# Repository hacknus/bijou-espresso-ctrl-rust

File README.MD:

### Bijou Espresso Machine Control Software (Rust Code)

This board controls the Bijou Espresso Machine.  
It is based around an STM32F405 microcontroller that reads out 5 PT100 RTDs (2 wire) using 5 MAX31865 ADCs.  
The temperature values are printed out over USB (CDC virtual COM Port) and shown on the SSD1306 OLED display.  
Two heating elements are controlled (SSR40 solid state relays) with PWM signals.  
Additionally a Buzzer and multiple LEDs can be controlled (PWM).

The software uses freertos-rust (wrapper for rust) and thus requires nightly to compile.  
The embedded-graphics crate is used for the display.

## Flashing the hardware (USB):

Setup a python environment in the project folder and install `pyserial`.

Update the `scripts/enter_bootloader.py` script to use the correct serial port for your system.

Connect the board using USB and then run

```
cargo run --release
```

in your python environment.

## Flashing the hardware (ST-Link debugger):

Create a `.cargo/config.toml` file according to this template:

```toml
[target.thumbv7em-none-eabihf]
runner = "arm-none-eabi-gdb -q -x openocd.gdb"
# uncomment these for other setups
# runner = "gdb-multiarch -q"
# runner = "gdb -q"

rustflags = [
    "-C", "link-arg=-Tlink.x"
]

[build]
target = "thumbv7em-none-eabihf"
```

specify your runner (depends on platform).

Connect the board using an ST-Link V3 (with TagConnect) to a USB port on the computer. Be sure to power the board with
an additional USB-C connector. (ST-Link does not provide power)  
First start the openocd server in a terminal/console window:
```openocd -f interface/stlink.cfg -f target/stm32f4x.cfg```   
Flash/Run the code on the hardware using:  
```cargo run --release```

## Notes on flashing/building

To set up your system, be sure to
follow [this rust embedded stm32 guide](https://docs.rust-embedded.org/discovery/f3discovery/03-setup/index.html)!  
Don't forget to install the [ARM GNU toolchain](https://developer.arm.com/downloads/-/arm-gnu-toolchain-downloads).

Now that the `rust-toolchain.toml` exists, the two steps below might not be necessary.  
Make sure you did
```rustup install nightly``` and
```rustup target add thumbv7em-none-eabihf --toolchain nightly``` to add the target to the nightly toolchain.

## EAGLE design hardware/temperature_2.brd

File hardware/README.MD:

## Electronics Hardware of Bijou Espresso Machine 

The main board schematic can be found in `main.sch` and the pcb layout in `main.brd`.  
The AC power measurement board schematic can be found in `AC_board.sch` and the pcb layout in `AC_board.brd`. This is currently not implemented (in software).  
The temperature readout board schematic can be found in `temperature_2.sch` and the pcb layout in `temperature_2.brd`.  
Issues:
- footprint of the mosfets for the LED (Switch) is faulty, needs to be fixed.
- capacitor missing on encoder
- temperature molex connector is the wrong way around (needs to be soldered from the back)
- attention! usb serial resistors are 22 Ohms, not 220 Ohms!!

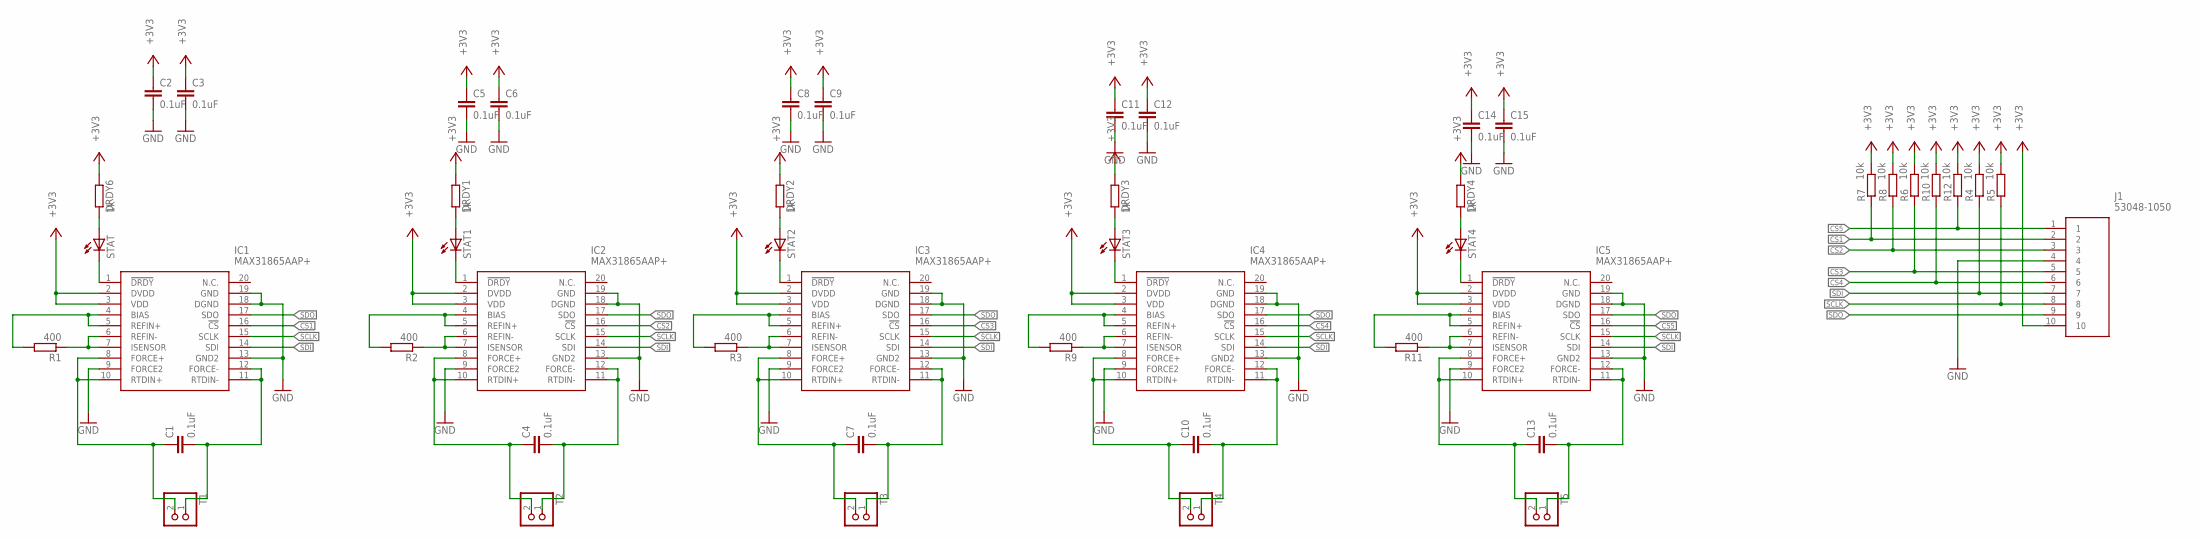
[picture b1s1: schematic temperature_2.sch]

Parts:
C1, C2, C3, C4, C5, C6, C7, C8, C9, C10, C11, C12, C13, C14, C15: 0.1uF; C0603K
DRDY1, DRDY2, DRDY3, DRDY4, DRDY6: 1k; R0603
IC1, IC2, IC3, IC4, IC5: MAX31865AAP+; SOP65P778X199-20N
J1: 53048-1050; SHDRRA10W25P0X125_1X10_1425X55
R1, R2, R3, R9, R11: 400; R1206
R4, R5, R6, R7, R8, R10, R12: 10k; R0603
STAT, STAT1, STAT2, STAT3, STAT4: LEDCHIPLED_0805; CHIPLED_0805
T1, T2, T3, T4, T5: PINHD-1X2; 1X02

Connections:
+3V3: C2.1, C3.1, C5.1, C6.1, C8.1, C9.1, C11.1, C12.1, C14.1, C15.1, DRDY1.1, DRDY2.1, DRDY3.1, DRDY4.1, DRDY6.1, IC1.2 (DVDD), IC1.3 (VDD), IC2.2 (DVDD), IC2.3 (VDD), IC3.2 (DVDD), IC3.3 (VDD), IC4.2 (DVDD), IC4.3 (VDD), IC5.2 (DVDD), IC5.3 (VDD), J1.10, R4.2, R5.2, R6.2, R7.2, R8.2, R10.2, R12.2
CS1: IC1.16 (!CS), J1.2, R7.1
CS2: IC2.16 (!CS), J1.3, R8.1
CS3: IC3.16 (!CS), J1.5, R6.1
CS4: IC4.16 (!CS), J1.6, R10.1
CS5: IC5.16 (!CS), J1.1, R12.1
GND: C2.2, C3.2, C5.2, C6.2, C8.2, C9.2, C11.2, C12.2, C14.2, C15.2, IC1.9 (FORCE2), IC1.13 (GND2), IC1.18 (DGND), IC1.19 (GND), IC2.9 (FORCE2), IC2.13 (GND2), IC2.18 (DGND), IC2.19 (GND), IC3.9 (FORCE2), IC3.13 (GND2), IC3.18 (DGND), IC3.19 (GND), IC4.9 (FORCE2), IC4.13 (GND2), IC4.18 (DGND), IC4.19 (GND), IC5.9 (FORCE2), IC5.13 (GND2), IC5.18 (DGND), IC5.19 (GND), J1.4
unnamed: IC2.4 (BIAS), IC2.5 (REFIN+), R2.2
unnamed: IC2.6 (REFIN-), IC2.7 (ISENSOR), R2.1
unnamed: C4.1, IC2.8 (FORCE+), IC2.10 (RTDIN+), T2.2
unnamed: C4.2, IC2.11 (RTDIN-), IC2.12 (FORCE-), T2.1
unnamed: IC3.4 (BIAS), IC3.5 (REFIN+), R3.2
unnamed: IC3.6 (REFIN-), IC3.7 (ISENSOR), R3.1
unnamed: C7.1, IC3.8 (FORCE+), IC3.10 (RTDIN+), T3.2
unnamed: C7.2, IC3.11 (RTDIN-), IC3.12 (FORCE-), T3.1
unnamed: IC4.4 (BIAS), IC4.5 (REFIN+), R9.2
unnamed: IC4.6 (REFIN-), IC4.7 (ISENSOR), R9.1
unnamed: C10.1, IC4.8 (FORCE+), IC4.10 (RTDIN+), T4.2
unnamed: C10.2, IC4.11 (RTDIN-), IC4.12 (FORCE-), T4.1
unnamed: IC5.4 (BIAS), IC5.5 (REFIN+), R11.2
unnamed: IC5.6 (REFIN-), IC5.7 (ISENSOR), R11.1
unnamed: C13.1, IC5.8 (FORCE+), IC5.10 (RTDIN+), T5.2
unnamed: C13.2, IC5.11 (RTDIN-), IC5.12 (FORCE-), T5.1
unnamed: DRDY6.2, STAT.A
unnamed: IC1.1 (!DRDY), STAT.C
unnamed: DRDY1.2, STAT1.A
unnamed: IC2.1 (!DRDY), STAT1.C
unnamed: DRDY2.2, STAT2.A
unnamed: IC1.4 (BIAS), IC1.5 (REFIN+), R1.2
unnamed: IC1.6 (REFIN-), IC1.7 (ISENSOR), R1.1
unnamed: IC3.1 (!DRDY), STAT2.C
unnamed: C1.1, IC1.8 (FORCE+), IC1.10 (RTDIN+), T1.2
unnamed: C1.2, IC1.11 (RTDIN-), IC1.12 (FORCE-), T1.1
unnamed: DRDY3.2, STAT3.A
unnamed: IC4.1 (!DRDY), STAT3.C
unnamed: DRDY4.2, STAT4.A
unnamed: IC5.1 (!DRDY), STAT4.C
SCLK: IC1.15 (SCLK), IC2.15 (SCLK), IC3.15 (SCLK), IC4.15 (SCLK), IC5.15 (SCLK), J1.8, R5.1
SDI: IC1.14 (SDI), IC2.14 (SDI), IC3.14 (SDI), IC4.14 (SDI), IC5.14 (SDI), J1.7, R4.1
SDO: IC1.17 (SDO), IC2.17 (SDO), IC3.17 (SDO), IC4.17 (SDO), IC5.17 (SDO), J1.9

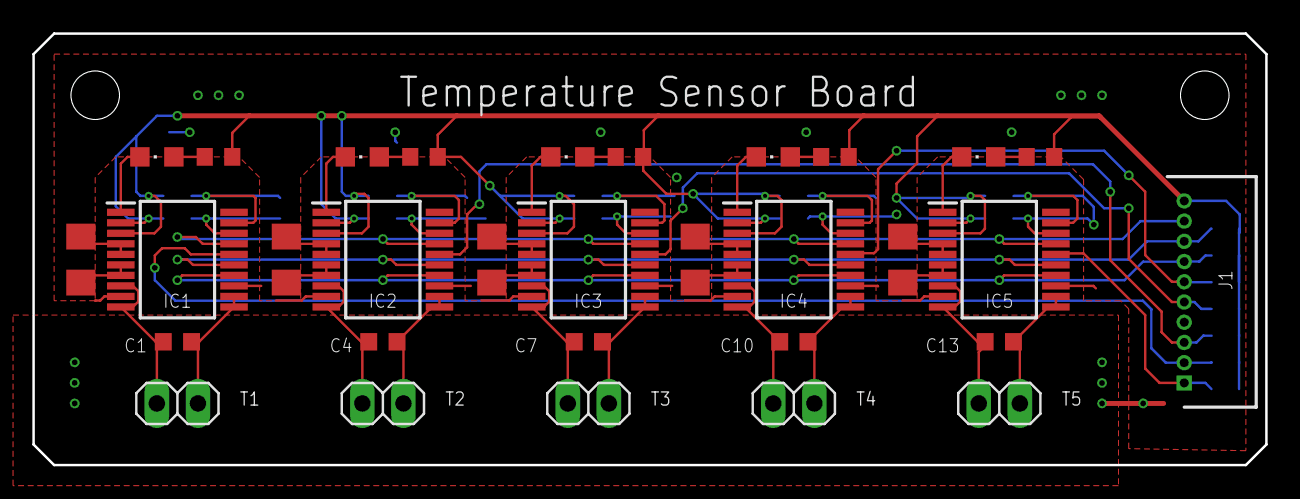
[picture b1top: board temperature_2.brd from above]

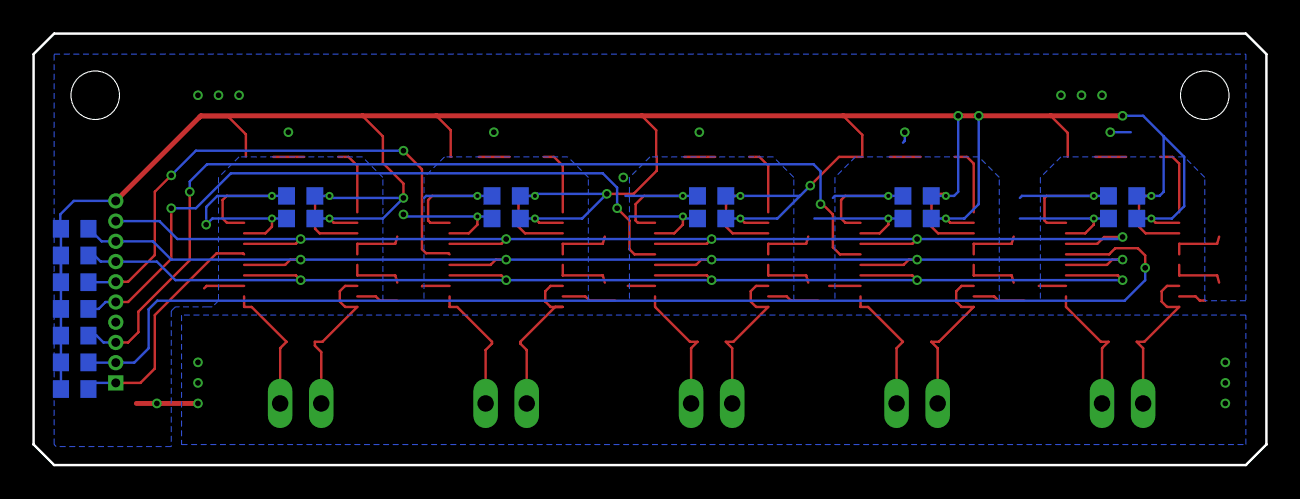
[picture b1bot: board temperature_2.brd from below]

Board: 2 copper layers, 76.2 x 26.7 mm, 48 parts (17 on the bottom side), 40 nets.

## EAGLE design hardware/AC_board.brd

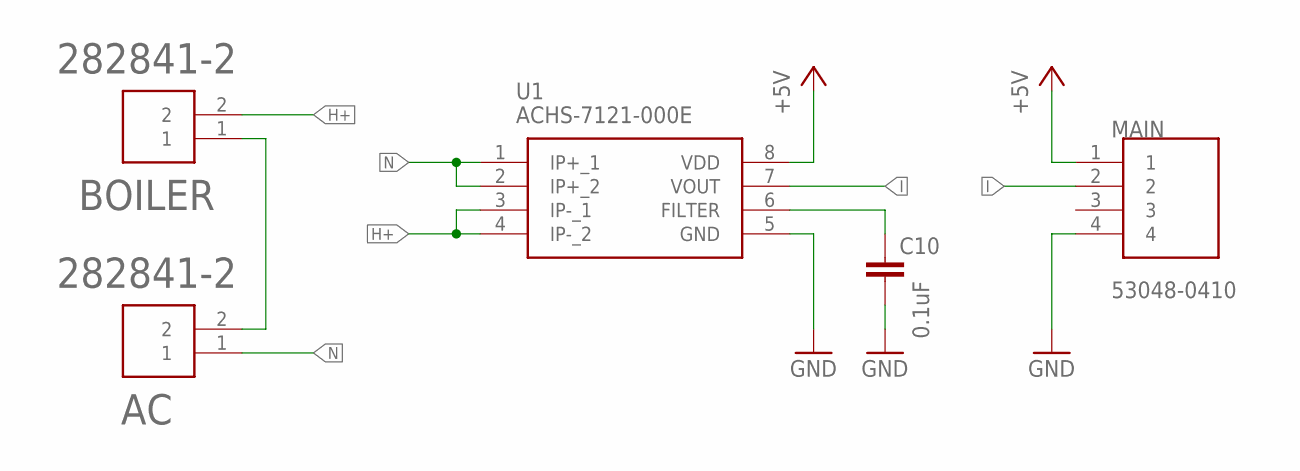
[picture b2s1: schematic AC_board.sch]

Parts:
AC: 282841-2; TE_282841-2
BOILER: 282841-2; TE_282841-2
C10: 0.1uF; C0603K
MAIN: 53048-0410; 530480410
U1: ACHS-7121-000E; SOIC127P606X204-8N

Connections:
+5V: MAIN.1, U1.8 (VDD)
GND: C10.2, MAIN.4, U1.5 (GND)
H+: BOILER.2, U1.3 (IP-_1), U1.4 (IP-_2)
I: MAIN.2, U1.7 (VOUT)
N: AC.1, U1.1 (IP+_1), U1.2 (IP+_2)
unnamed: C10.1, U1.6 (FILTER)
unnamed: AC.2, BOILER.1

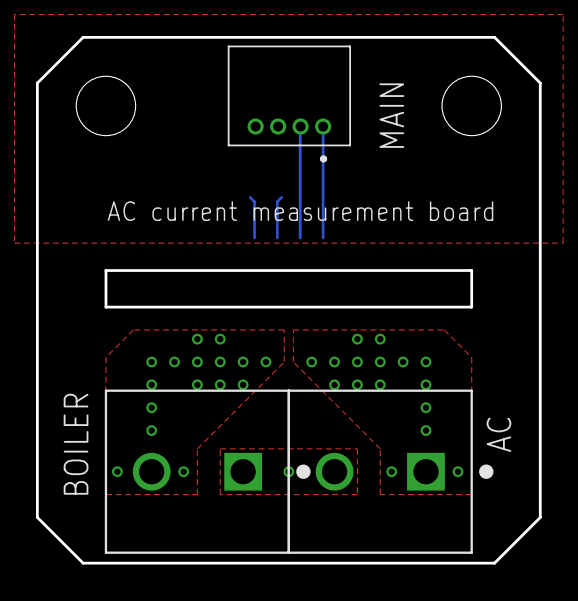
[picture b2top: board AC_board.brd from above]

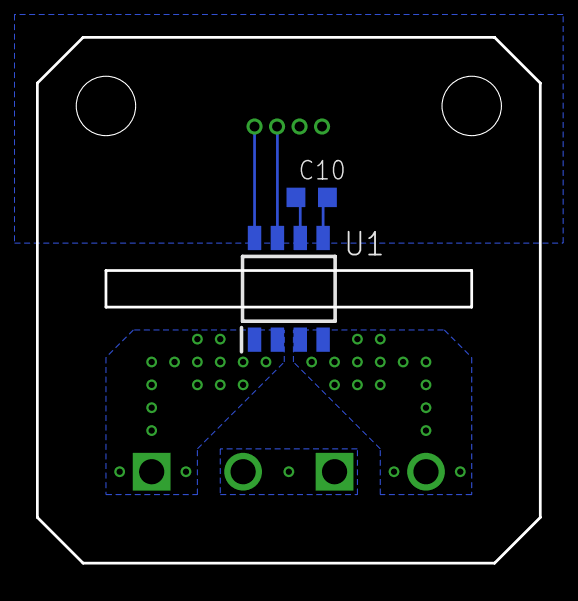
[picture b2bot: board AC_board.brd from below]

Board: 2 copper layers, 27.9 x 29.2 mm, 5 parts (2 on the bottom side), 7 nets.

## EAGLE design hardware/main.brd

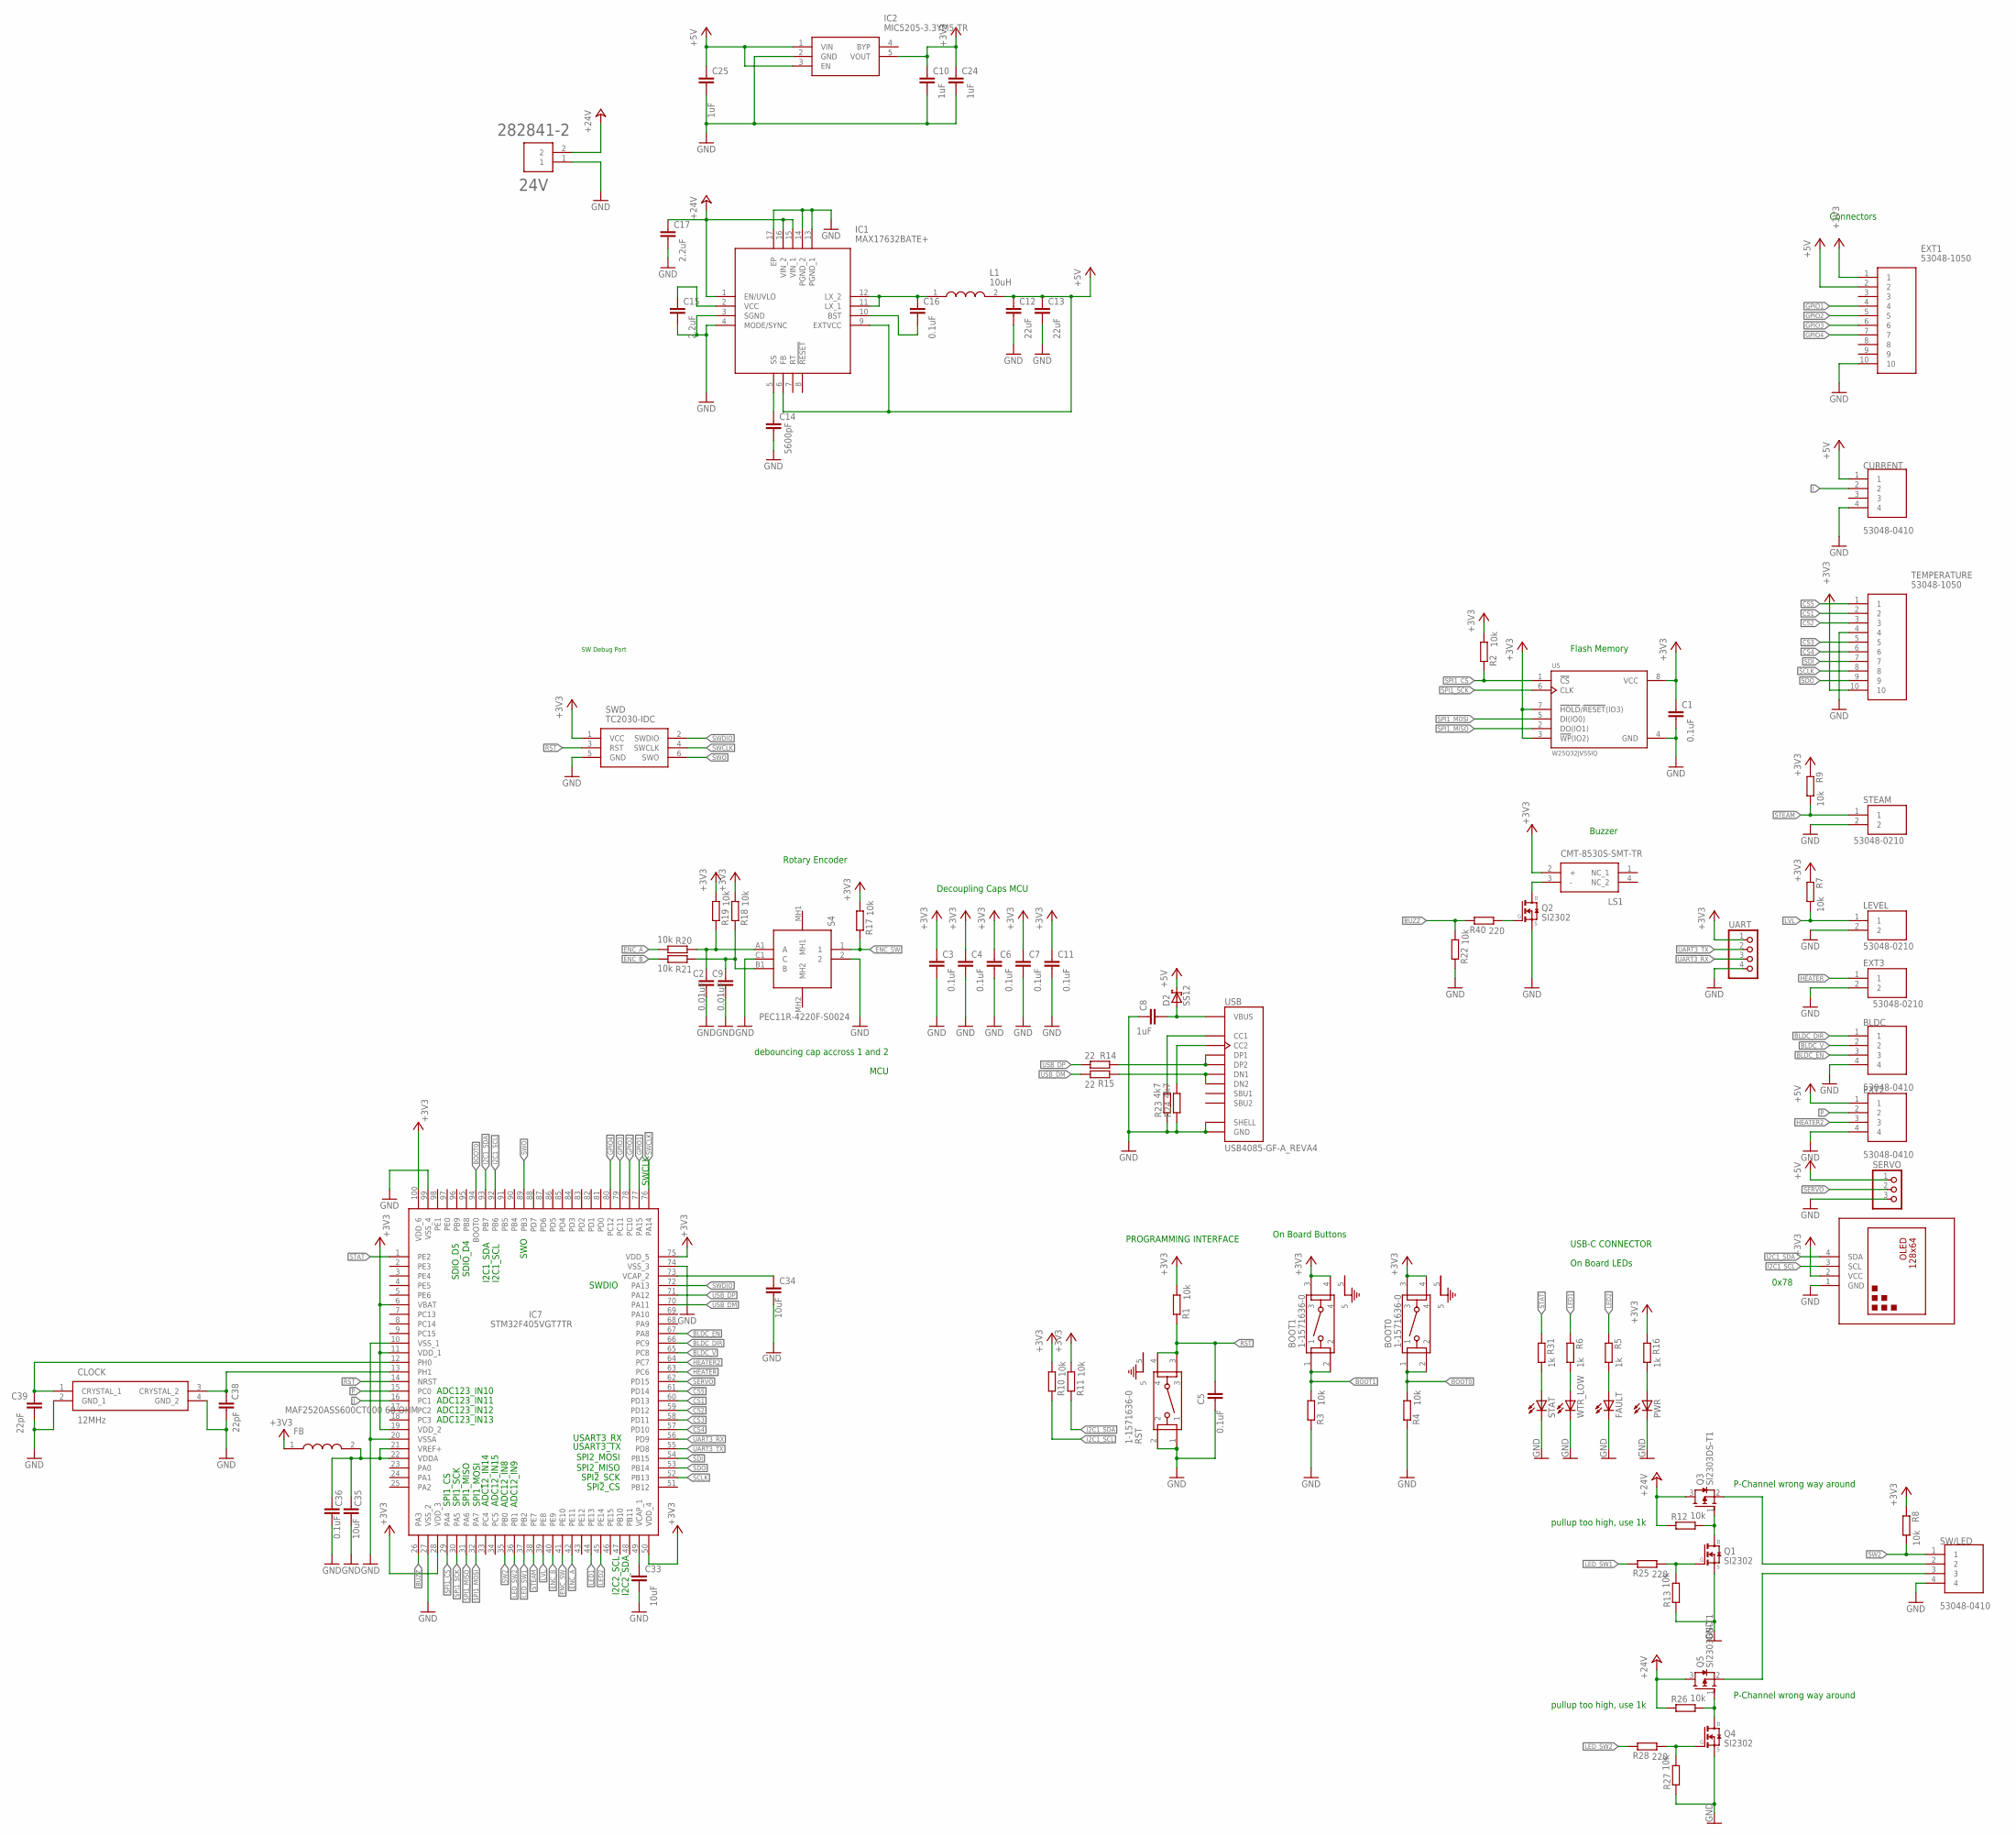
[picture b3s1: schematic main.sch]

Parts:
24V: 282841-2; TE_282841-2
BLDC: 53048-0410; 530480410
BOOT0, BOOT1: 1-1571636-0; SW5_1571636
C1, C3, C4, C5, C6, C7, C11, C16, C36: 0.1uF; C0603K
C2, C9: 0.01uF; C0603K
C8, C10, C24, C25: 1uF; C0603K
C12, C13: 22uF; C0603K
C14: 5600pF; C0603K
C15, C17: 2.2uF; C0603K
C33, C34, C35: 10uF; C0603K
C38, C39: 22pF; C0603K
CLOCK: 12MHz; ABM8AIG8000MHZ1ZT
CURRENT: 53048-0410; 530480410
D2: SS12; DO214AC
DISPLAY: DISPLAY-OLED-128X64-I2C
EXT1: 53048-1050; SHDRRA10W25P0X125_1X10_1425X55
EXT2: 53048-0410; 530480410
EXT3: 53048-0210; SHDRRA2W35P0X125_1X2_425X550X3
FAULT: LEDCHIPLED_0805; CHIPLED_0805
FB: MAF2520ASS600CT000 60 OHM; INDC2520X120N
IC1: MAX17632BATE+; QFN50P300X300X80-17N
IC2: MIC5205-3.3YM5-TR; SOT95P280X145-5N
IC7: STM32F405VGT7TR; QFP50P1600X1600X160-100N
L1: 10uH; INDC3225X270N
LEVEL: 53048-0210; SHDRRA2W35P0X125_1X2_425X550X3
LS1: CMT-8530S-SMT-TR; CMT8530SSMTTR
PWR: LEDCHIPLED_0805; CHIPLED_0805
Q1, Q2, Q4: SI2302; SOT23
Q3, Q5: SI2303DS-T1; SOT90P248X115-3N
R1, R2, R3, R4, R7, R8, R9, R10, R11, R12, R13, R17, R18, R19, R20, R21, R22, R26, R27: 10k; R0603
R5, R6, R16, R31: 1k; R0603
R14, R15: 22; R0603
R23, R24: 4k7; R0603
R25, R28, R40: 220; R0603
RST: 1-1571636-0; SW5_1571636
S4: PEC11R-4220F-S0024; PEC11R4220FS0024
SERVO: PINHD-1X3/90; 1X03/90
STAT: LEDCHIPLED_0805; CHIPLED_0805
STEAM: 53048-0210; SHDRRA2W35P0X125_1X2_425X550X3
SW/LED: 53048-0410; 530480410
SWD: TC2030-IDC; TC2030IDC
TEMPERATURE: 53048-1050; SHDRRA10W25P0X125_1X10_1425X55
U5: W25Q32JVSSIQ; SOIC127P790X216-8N
UART: PINHD-1X4; 1X04
USB: USB4085-GF-A_REVA4; GCT_USB4085-GF-A_REVA4
WTR_LOW: LEDCHIPLED_0805; CHIPLED_0805

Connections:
+3V3: BOOT0.3, BOOT0.4, BOOT1.3, BOOT1.4, C1.1, C3.1, C4.1, C6.1, C7.1, C10.1, C11.1, C24.1, DISPLAY.2 (VCC), EXT1.1, FB.1, IC2.5 (VOUT), IC7.6 (VBAT), IC7.11 (VDD_1), IC7.19 (VDD_2), IC7.28 (VDD_3), IC7.50 (VDD_4), IC7.75 (VDD_5), IC7.100 (VDD_6), LS1.2 (+), R1.2, R2.2, R7.1, R8.1, R9.1, R10.2, R11.2, R16.1, R17.2, R18.2, R19.2, SWD.1 (VCC), TEMPERATURE.10, U5.3 (!WP!(IO2)), U5.7 (!HOLD!/!RESET!(IO3)), U5.8 (VCC), UART.1
+5V: C12.1, C13.1, C25.1, CURRENT.1, D2.C, EXT1.2, EXT2.1, IC1.6 (FB), IC1.9 (EXTVCC), IC2.1 (VIN), IC2.3 (EN), L1.2, SERVO.1
+24V: 24V.2, C17.1, IC1.1 (EN/UVLO), IC1.15 (VIN_1), IC1.16 (VIN_2), Q3.3 (D), Q5.3 (D), R12.1, R26.1
BLDC_DIR: BLDC.1, IC7.66 (PC9)
BLDC_EN: BLDC.3, IC7.67 (PA8)
BLDC_V: BLDC.2, IC7.65 (PC8)
BOOT0: BOOT0.1, BOOT0.2, IC7.94 (BOOT0), R4.2
BOOT1: BOOT1.1, BOOT1.2, R3.2
BUZZ: IC7.26 (PA3), R22.2, R40.1
CS1: IC7.60 (PD13), TEMPERATURE.2
CS2: IC7.59 (PD12), TEMPERATURE.3
CS3: IC7.58 (PD11), TEMPERATURE.5
CS4: IC7.57 (PD10), TEMPERATURE.6
CS5: IC7.61 (PD14), TEMPERATURE.1
ENC_A: IC7.42 (PE11), R20.2
ENC_B: IC7.40 (PE9), R21.2
ENC_SW: IC7.41 (PE10), R17.1, S4.1
GND: 24V.1, BLDC.4, C1.2, C2.2, C3.2, C4.2, C5.2, C6.2, C7.2, C8.1, C9.2, C10.2, C11.2, C12.2, C13.2, C14.2, C15.2, C17.2, C24.2, C25.2, C33.2, C34.2, C35.2, C36.2, C38.2, C39.2, CLOCK.2 (GND_1), CLOCK.4 (GND_2), CURRENT.4, DISPLAY.1 (GND), EXT1.10, EXT2.4, EXT3.2, FAULT.C, IC1.3 (SGND), IC1.4 (MODE/SYNC), IC1.13 (PGND_1), IC1.14 (PGND_2), IC1.17 (EP), IC2.2 (GND), IC7.10 (VSS_1), IC7.20 (VSSA), IC7.27 (VSS_2), IC7.74 (VSS_3), IC7.99 (VSS_4), LEVEL.2, PWR.C, Q1.2 (S), Q2.2 (S), Q4.2 (S), R3.1, R4.1, R13.1, R22.1, R23.1, R24.1, R27.1, RST.1, RST.2, S4.2, S4.C1 (C), SERVO.3, STAT.C, STEAM.2, SW/LED.4, SWD.5 (GND), TEMPERATURE.4, U5.4 (GND), UART.4, USB.A1 (GND), USB.A12 (GND), USB.B1 (GND), USB.B12 (GND), USB.P1 (SHELL), USB.P2 (SHELL), USB.P3 (SHELL), USB.P4 (SHELL), WTR_LOW.C
GPIO1: EXT1.4, IC7.77 (PA15)
GPIO2: EXT1.5, IC7.78 (PC10)
GPIO3: EXT1.6, IC7.79 (PC11)
GPIO4: EXT1.7, IC7.80 (PC12)
HEATER: EXT3.1, IC7.63 (PC6)
HEATER2: EXT2.3, IC7.64 (PC7)
I: CURRENT.2, IC7.16 (PC1)
I2C1_SCL: DISPLAY.3 (SCL), IC7.92 (PB6), R10.1
I2C1_SDA: DISPLAY.4 (SDA), IC7.93 (PB7), R11.1
LED1: IC7.44 (PE13), R6.1
LED2: IC7.45 (PE14), R5.1
LED_SW1: IC7.37 (PB2), R25.1
LED_SW2: IC7.36 (PB1), R28.1
LVL: IC7.39 (PE8), LEVEL.1, R7.2
unnamed: R14.1, USB.A6 (DP1), USB.B6 (DP2)
unnamed: R15.1, USB.A7 (DN1), USB.B7 (DN2)
unnamed: R24.2, USB.B5 (CC2)
unnamed: R23.2, USB.A5 (CC1)
unnamed: LS1.3 (-), Q2.3 (D)
unnamed: R6.2, WTR_LOW.A
unnamed: PWR.A, R16.2
unnamed: FAULT.A, R5.2
unnamed: R31.2, STAT.A
unnamed: C9.1, R18.1, R21.1, S4.B1 (B)
unnamed: C14.1, IC1.5 (SS)
unnamed: C2.1, R19.1, R20.1, S4.A1 (A)
unnamed: C16.2, IC1.10 (BST)
unnamed: C8.2, D2.A, USB.A4 (VBUS), USB.A9 (VBUS), USB.B4 (VBUS), USB.B9 (VBUS)
unnamed: Q1.3 (D), Q3.1 (G), R12.2
unnamed: C15.1, IC1.2 (VCC)
unnamed: C16.1, IC1.11 (LX_1), IC1.12 (LX_2), L1.1
unnamed: Q1.1 (G), R13.2, R25.2
unnamed: C34.1, IC7.73 (VCAP_2)
unnamed: Q4.3 (D), Q5.1 (G), R26.2
unnamed: Q4.1 (G), R27.2, R28.2
unnamed: C35.1, C36.1, FB.2, IC7.21 (VREF+), IC7.22 (VDDA)
unnamed: Q3.2 (S), SW/LED.2
unnamed: Q5.2 (S), SW/LED.3
unnamed: Q2.1 (G), R40.2
unnamed: C33.1, IC7.49 (VCAP_1)
unnamed: C38.1, CLOCK.3 (CRYSTAL_2), IC7.13 (PH1)
unnamed: C39.1, CLOCK.1 (CRYSTAL_1), IC7.12 (PH0)
P: EXT2.2, IC7.15 (PC0)
RST: C5.1, IC7.14 (NRST), R1.1, RST.3, RST.4, SWD.3 (RST)
SCLK: IC7.52 (PB13), TEMPERATURE.8
SDI: IC7.54 (PB15), TEMPERATURE.7
SDO: IC7.53 (PB14), TEMPERATURE.9
SERVO: IC7.62 (PD15), SERVO.2
SPI1_CS: IC7.29 (PA4), R2.1, U5.1 (!CS)
SPI1_MISO: IC7.31 (PA6), U5.2 (DO(IO1))
SPI1_MOSI: IC7.32 (PA7), U5.5 (DI(IO0))
SPI1_SCK: IC7.30 (PA5), U5.6 (CLK)
STAT: IC7.1 (PE2), R31.1
STEAM: IC7.38 (PE7), R9.2, STEAM.1
SW2: IC7.35 (PB0), R8.2, SW/LED.1
SWCLK: IC7.76 (PA14), SWD.4 (SWCLK)
SWDIO: IC7.72 (PA13), SWD.2 (SWDIO)
SWO: IC7.89 (PB3), SWD.6 (SWO)
UART3_RX: IC7.56 (PD9), UART.3
UART3_TX: IC7.55 (PD8), UART.2
USB_DM: IC7.70 (PA11), R15.2
USB_DP: IC7.71 (PA12), R14.2

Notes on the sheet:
I2C1_SDA
I2C1_SCL
I2C2_SCL
I2C2_SDA
SPI1_CS
SPI1_SCK
SPI1_MISO
SPI1_MOSI
SPI2_CS
SPI2_SCK
SPI2_MISO
SPI2_MOSI
SWDIO
SWCLK
SWO
SDIO_D4
SDIO_D5
ADC123_IN10
ADC123_IN11
ADC123_IN12
ADC123_IN13
ADC12_IN14
ADC12_IN15
ADC12_IN8
ADC12_IN9
USART3_TX
USART3_RX
SW Debug Port
Buzzer
Flash Memory
On Board Buttons
On Board LEDs
Connectors
Decoupling Caps MCU
MCU
Rotary Encoder
USB-C CONNECTOR
PROGRAMMING INTERFACE
0x78
debouncing cap accross 1 and 2

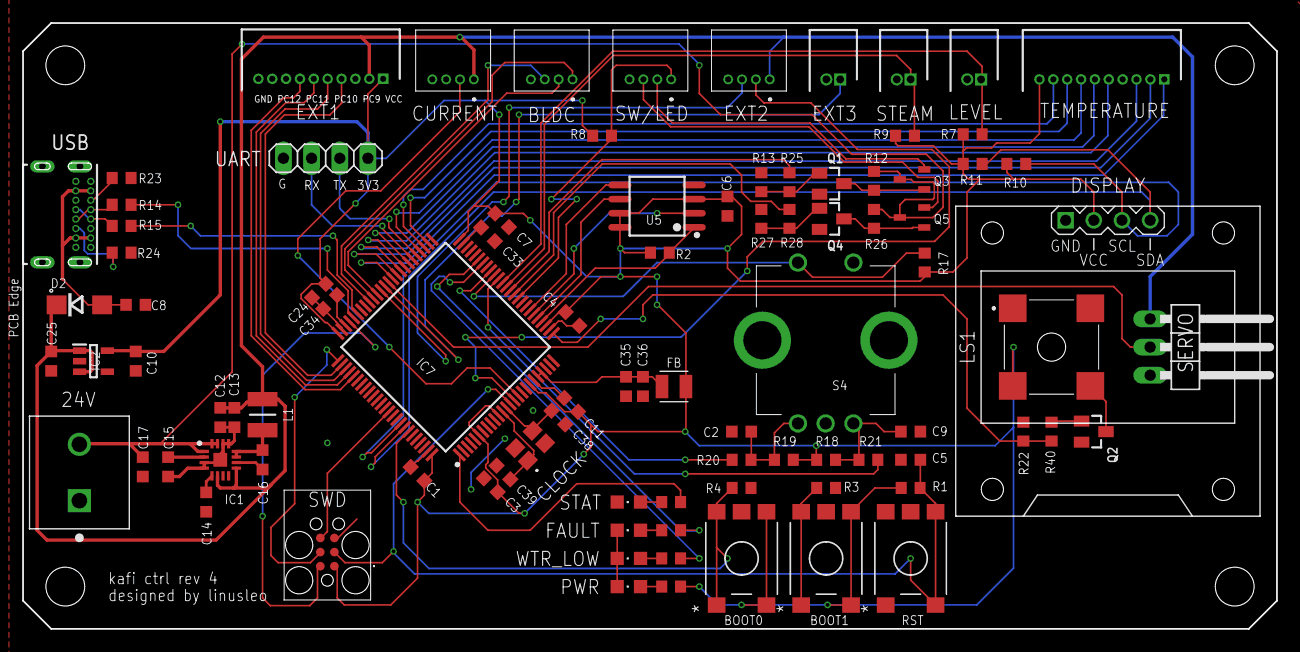
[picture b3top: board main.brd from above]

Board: 2 copper layers, 113.0 x 54.6 mm, 92 parts (0 on the bottom side), 80 nets.

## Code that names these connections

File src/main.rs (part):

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    let gpioe = dp.GPIOE.split();

    // initialize leds
    let mut stat_led = LED::new(gpioe.pe2.into_push_pull_output());
    let mut fault_1_led = LED::new(gpioe.pe13.into_push_pull_output());
    let mut fault_2_led = LED::new(gpioe.pe14.into_push_pull_output());

    let mut tick_timer = dp.TIM5.counter_ms(&clocks);
    tick_timer.start(60000.millis()).unwrap(); // set the timeout to 31 days
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    let dma2 = StreamsTuple::new(dp.DMA2);

    // initialize pins
    let cs_5 = gpiod.pd14.into_push_pull_output();
    let cs_4 = gpiod.pd10.into_push_pull_output();
    let cs_3 = gpiod.pd11.into_push_pull_output();
    let cs_2 = gpiod.pd12.into_push_pull_output();
    let cs_1 = gpiod.pd13.into_push_pull_output();
    let mut bldc_en = gpioa.pa8.into_push_pull_output();
    let mut bldc_dir = gpioc.pc9.into_push_pull_output();
    bldc_dir.set_low();
    let water_low = false; // TODO: implement water_low pin
    let heater_1 = Channel1::new(gpioc.pc6);
    let heater_2 = Channel2::new(gpioc.pc7);
    let heater_bg = Channel4::new(gpiod.pd15); // fix because pa2 is broken

    let lever = gpioe.pe7.into_floating_input();
    let bldc_v = Channel3::new(gpioc.pc8);
    let buzz = Channel4::new(gpioa.pa3);
    let led_dim = Channel4::new(gpiob.pb1);

    let enc_pin_a = gpioe.pe11.into_floating_input();
    let mut enc_pin_b = gpioe.pe9.into_floating_input();
    let _enc_pin_sw = gpioe.pe10.into_floating_input();
    let mut syscfg = dp.SYSCFG.constrain();
    enc_pin_b.make_interrupt_source(&mut syscfg);
    enc_pin_b.trigger_on_edge(&mut dp.EXTI, Edge::RisingFalling);
    enc_pin_b.enable_interrupt(&mut dp.EXTI);

    // initialize button
    let button = gpiob.pb0.into_floating_input();

    // initialize extension pins
    let _pin_a_15 = gpioa.pa15.into_push_pull_output();
    let mut valve1_pin = gpioc.pc10.into_push_pull_output();
    let mut valve2_pin = gpioc.pc11.into_push_pull_output();
    let _pin_c_12 = gpioc.pc12.into_push_pull_output();

    valve1_pin.set_high();
    valve2_pin.set_high();
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        usb_global: dp.OTG_FS_GLOBAL,
        usb_device: dp.OTG_FS_DEVICE,
        usb_pwrclk: dp.OTG_FS_PWRCLK,
        pin_dm: stm32f4xx_hal::gpio::alt::otg_fs::Dm::PA11(gpioa.pa11.into_alternate()),
        pin_dp: stm32f4xx_hal::gpio::alt::otg_fs::Dp::PA12(gpioa.pa12.into_alternate()),
        hclk: clocks.hclk(),
    };

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
    let mut pos: isize = 0;

    let scl = gpiob.pb6;
    let sda = gpiob.pb7;
    // initialize i2c
    let i2c = dp.I2C1.i2c(
        (scl, sda),
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    display.init().unwrap();

    // Initialize SPI1 for the flash memory
    let sck_1 = gpioa.pa5;
    let miso_1 = gpioa.pa6;
    let mosi_1 = gpioa.pa7;
    let cs_flash = gpioa.pa4.into_push_pull_output();

    // Initialize SPI1
    let spi1 = dp
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
    let spi1_bus = shared_bus::BusManagerSimple::new(spi1);

    let sclk_2 = gpiob.pb13;
    let sdo_2 = gpiob.pb14;
    let sdi_2 = gpiob.pb15;

    // initialize spi
    let spi2 = dp.SPI2.spi(
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    let spi2_bus = shared_bus::BusManagerSimple::new(spi2);

    // init adc
    let pressure_sense_pin = gpioc.pc0.into_analog();
    let current_sense_pin = gpioc.pc1.into_analog();

    let dma_config = DmaConfig::default()
        .transfer_complete_interrupt(true)
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
    let dp = Peripherals::steal();

    // Turn off the Heater, it's connected to pin PC6.
    // initialize ports
    dp.GPIOC.odr.write(|w| w.odr6().clear_bit());
    dp.GPIOE.odr.write(|w| w.odr4().clear_bit());
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
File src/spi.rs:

use core::cell::RefCell;
use arrform::{arrform, ArrForm};
use cortex_m::interrupt::Mutex;
use stm32f4xx_hal::{
    pac::SPI2,
    spi::{Error, Spi, Phase, Polarity, Mode as spiMode},
    gpio::{Output, PB13, PB14, PB15, Pin},
    rcc::Clocks,
    prelude::*,
};

use crate::usb_println;

pub static SPI_BUS: Mutex<RefCell<Option<Spi<SPI2, (PB13, PB14, PB15)>>>> =
    Mutex::new(RefCell::new(None));

pub fn spi2_init(spi2: SPI2, sclk: PB13, sdo: PB14, sdi: PB15, clocks: &Clocks) {
    let spi: Spi<SPI2, (PB13, PB14, PB15)> = spi2.spi(
        (sclk, sdo, sdi),
        spiMode {
            polarity: Polarity::IdleHigh,
            phase: Phase::CaptureOnSecondTransition,
        },
        10.kHz(),
        clocks,
    );
    cortex_m::interrupt::free(|cs| {
        *SPI_BUS.borrow(cs).borrow_mut() = Some(spi);
    });
}

pub fn spi_write<const P: char, const N: u8>(cs_pin: &mut Pin<P, N, Output>, register: u8, payload: u8) -> Result<u8, Error> {
    cortex_m::interrupt::free(|cs| {
        match SPI_BUS.borrow(cs).borrow_mut().as_mut() {
            None => { Err(Error::ModeFault) }
            Some(spi) => {
                cs_pin.set_low();
                let mut status_byte = 0;
                let mut buffer: [u8; 2] = [register | 0x80, payload];
                // usb_println(arrform!(64,"write buffer {:?}",buffer).as_str());
                match spi.transfer(&mut buffer) {
                    Ok(r) => {
                        //usb_println(arrform!(64,"write answer {:?}",r).as_str());
                        status_byte = r[0];
                    }
                    Err(err) => {
                        //usb_println(arrform!(64, "spi failed to write = {:?}", err).as_str());
                    }
                }
                cs_pin.set_high();
                Ok(status_byte)
            }
        }
    })
}

pub fn spi_read<const P: char, const N: u8>(cs_pin: &mut Pin<P, N, Output>, register: u8, buffer: &mut [u8]) -> Result<u8, Error> {
    buffer[0] = register;
    cortex_m::interrupt::free(|cs| {
        match SPI_BUS.borrow(cs).borrow_mut().as_mut() {
            None => { Err(Error::ModeFault) }
            Some(spi) => {
                cs_pin.set_low();
                //usb_println(arrform!(64,"write buffer {:?}",read_cmd).as_str());
                match spi.transfer(buffer) {
                    Ok(r) => {
                        //usb_println(arrform!(64,"read answer {:?}",r).as_str());
                    }
                    Err(err) => {
                        //usb_println(arrform!(64, "spi failed to read = {:?}", err).as_str());
                    }
                }
                cs_pin.set_high();
                Ok(0)
            }
        }
    })
}

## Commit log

2023-01-03 Initial commit (compiles)
2023-01-06 freertos is not working with usb
2023-01-14 first test with freertos
2023-01-15 screen is working (timer/tick not!)
2023-01-15 timer/tick count is working!
2023-01-15 PT100 readout works now.
2023-01-17 implement PWM
2023-01-17 minor edit
2023-01-17 add inverted bmp
2023-01-17 not sure if this file is needed...
2023-01-17 updated README.MD, added TODO
2023-01-17 added hardware files of the electronics
2023-01-17 move .bmp in images folder
2023-01-18 quick update
2023-01-19 add remarks to README.MD
2023-01-19 implement mutex for temperature data to be shared between tasks
2023-01-19 bug fix!
2023-01-19 put in TODOs!
2023-01-20 implemented encoder with interrupt
2023-01-20 comment encoder interrupt
2023-01-21 clean up
2023-01-21 add ulils structs
2023-01-21 derive Debug
2023-01-21 command structure / housekeeping printing over USB
2023-01-21 implement usb task
2023-01-22 adabt states
2023-01-22 implement bldc timer and LED task
2023-01-22 more commands / states / clean-up
2023-01-28 implement more commands (new value extraction from cmd)
2023-01-28 code clean up
2023-01-28 convert result to option
2023-01-29 clean up code and full control implemented
2023-05-16 add fault detection
2023-09-29 major update
2023-09-29 add software scheme
2023-09-29 split command queue
2023-09-29 add toolchain
2023-09-29 update max31865 temperature readout
2023-09-29 update command response
2023-09-30 update temperature task
2023-09-30 simplify
2023-10-01 update valve and heating tasks
2023-10-01 add a todo
2024-01-27 prefix for unused variables
2024-01-27 fix valve commanding and overrides
2024-01-27 fix valave pins
2024-01-27 also start heating via cmd
2024-01-27 fix valves
2024-01-27 read button
2024-01-27 pid to pd
2024-01-27 fix pump override
2024-01-27 fix bldc
2024-01-27 fix pwm
2024-01-27 pid to pi
2024-01-27 switch two valves
2024-01-27 fix pump ctrl
2024-01-27 implement lever
2024-01-28 implemented lever
2024-02-18 adjust PID
2024-02-18 increase pre infuse power
2024-02-18 fix heating threshold
2024-02-18 fix heating condition
2024-02-18 parameter update
2024-02-18 implement second PID
2024-02-18 increase target during extraction
2024-03-04 implement pressure sensor
2024-05-20 change pre-infuse power/timer
2025-03-11 implement other PID loops
2025-03-14 implement PID commands
2025-03-14 adjusted stack size and timer timeout
2025-03-14 implement MAV
2025-03-15 adjust state update
2025-03-16 debug Pressure
2025-05-18 fix pressure adc
2025-05-18 fix statemachine
2025-06-04 implement flash memory
2025-06-04 adjust default values
2025-06-04 fix override not happening
2025-06-05 fix heap
2025-06-12 set 10% PID offset
2025-06-12 add pid hk for tuning
2025-06-13 update pid more often
2025-06-13 smoother LED
2025-06-17 reduce pump power
2025-06-29 still with overshoot
2025-08-03 increase power again
2025-08-03 increase pressure and increase kD for heater 1 PID
2025-08-03 print pid 1 parameters
2025-08-03 subtract d
2025-08-03 increase d
2025-08-03 fix f32/u32
2025-08-03 scale factor
2025-08-03 fix d and i part
2025-08-08 fix timer
2025-08-08 Revert "fix timer"
    This reverts commit 338b305cba78293b5eaf216dc8308b49e98d38f3.
2025-08-08 fix timer, correct way!
2025-08-08 slightly decrease pressure and set kd for brew group
2026-04-19 test steam
2026-04-19 fix long press
2026-04-19 fix enc dir and LED states
2026-04-19 fix PID
2026-04-19 fix steam power
2026-04-19 fix pump power
2026-04-19 fix states and increase steam temp
2026-04-19 increase steam temp
2026-04-19 increase steam temp to 150
2026-04-21 show state on display
2026-04-21 adjust steam power
2026-04-21 fix states
2026-04-21 fix extraction in coffee ready state
2026-04-21 change enc start val to > 1
2026-04-28 change PWM to PA1 (Channel 2) because we fried PA2
2026-04-29 set heater to pd15 (servo pin)
2026-04-29 adjust steam power, for correct steaming
2026-04-29 implement buzzer
2026-04-29 increase stack

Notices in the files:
parts and their libraries:
diy-modules: Released under the Creative Commons Attribution 4.0 International License: http://creativecommons.org/licenses/by/4.0
COPYRIGHT: Copyright (C) 2016 Accelerated Designs. All rights reserved
